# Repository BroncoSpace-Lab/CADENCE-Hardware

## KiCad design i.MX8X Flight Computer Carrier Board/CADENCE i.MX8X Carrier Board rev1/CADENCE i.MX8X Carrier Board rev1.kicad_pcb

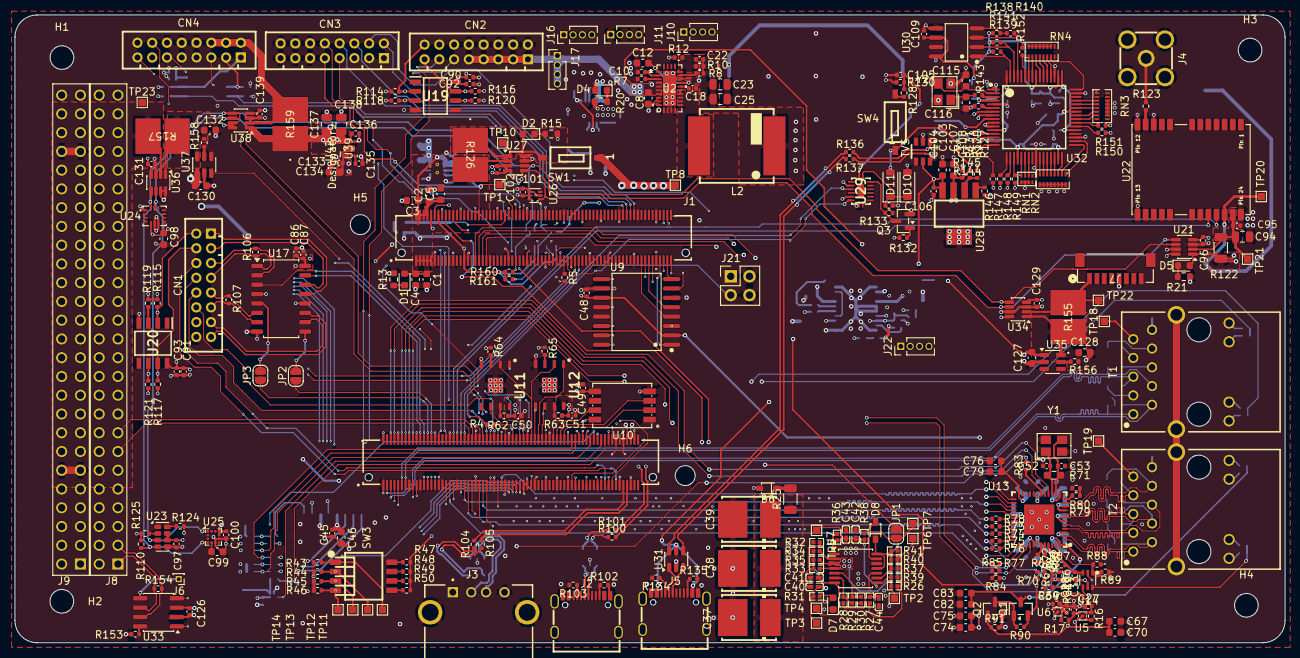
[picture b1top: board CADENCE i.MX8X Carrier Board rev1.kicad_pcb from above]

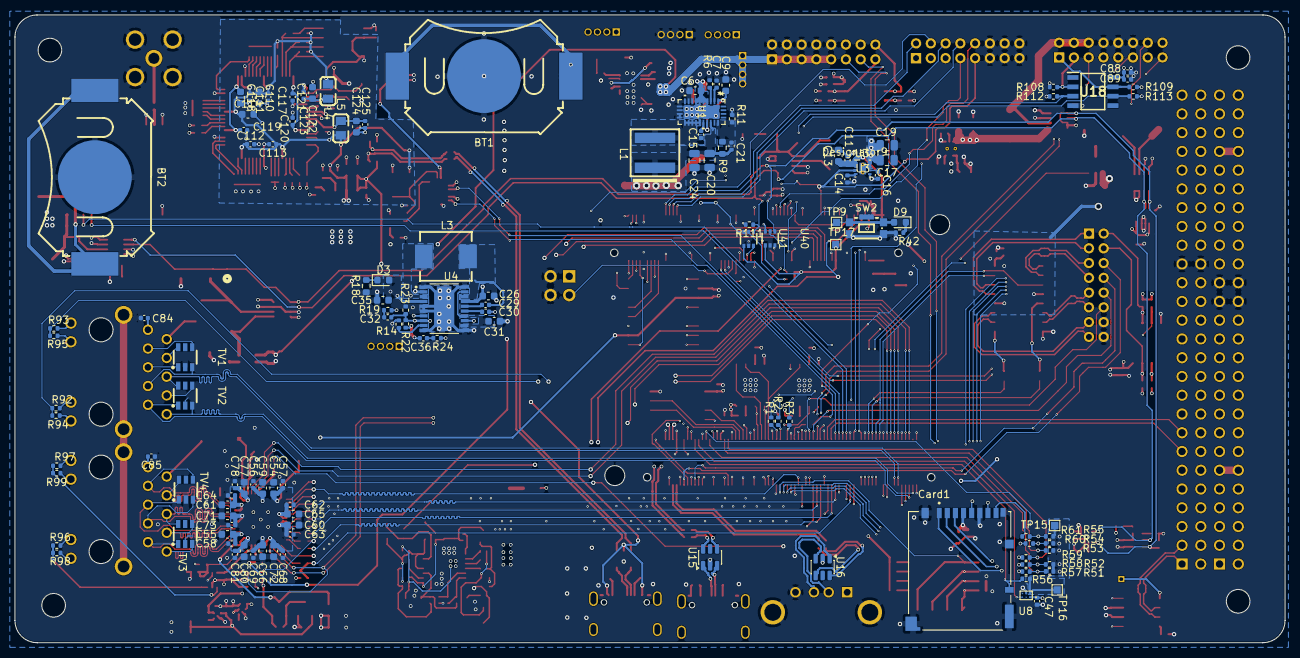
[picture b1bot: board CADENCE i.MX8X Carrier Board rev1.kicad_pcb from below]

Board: 6 copper layers, 172.0 x 85.0 mm, 431 parts (125 on the bottom side), 352 nets.

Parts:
BT1, BT2: Battery_Cell; BAT-SMD_MY-2032-11
C1, C2: 22uF; C_0603_1608Metric
C3, C4, C6, C8, C13, C26, C31, C110, C118, C122, C124, C134: 4.7uF; C_0603_1608Metric
C5, C35, C114: 100nF; C_0603_1608Metric
C7, C10: 10nF; C_0402_1005Metric
C9, C12, C54, C55, C59, C60, C61, C65, C66, C71, C72, C77, C80, C107, C128, C132: 1uF; C_0603_1608Metric
C11, C14, C15, C16, C18, C27, C28, C29, C30, C33, C34, C45, C47, C48, C49, C50, C51, C56, C57, C58, C62, C63, C64, C68, C69, C73, C78, C81, C84, C85, C87, C89, C92, C93, C95, C96, C97, C100, C101, C102, C104, C105, C106, C108, C109, C111, C112, C113, C117, C119, C120, C121, C123, C125, C126, C129, C131, C133, C135, C136, C139: 100nF; C_0402_1005Metric
C17, C19, C137, C138: 22uF; C_0805_2012Metric
C20, C23, C24, C25: 47uF; C_0805_2012Metric
C21: 4.7pF; C_0402_1005Metric
C22: 10pF; C_0402_1005Metric
C32, C86, C88, C90, C91: 1nF; C_0402_1005Metric
C36: 33pF; C_0402_1005Metric
C37, C38, C39: 100uF; CAP-SMD_L7.3-W6.1_TCN4227M025R0100
C40, C41, C42, C43, C44: 10u; C0402
C46, C70, C75, C79, C83, C127, C130: 10uF; C_0603_1608Metric
C52, C53: 18pF; C_0402_1005Metric
C67, C74, C76, C82: 10nF; C_0603_1608Metric
C94: 10u; C_0805_2012Metric
C98: 10u; C_0603_1608Metric
C99: 220nF; C_0603_1608Metric
C103: 2.2uF; C_0603_1608Metric
C115, C116: 12pF; C_0603_1608Metric
CN1, CN2, CN3, CN4: DF11-16DP-2DSA(08); CONN-TH_DF11-16DP-2DSA-08
Card1: HRS DM3BT-DSF-PEJS; HRS_DM3BT-DSF-PEJS
D1, D5, D9: RED; LED_0603_1608Metric
D2, D4, D7: GREEN; LED_0603_1608Metric
D3: BLUE; LED_0603_1608Metric
D6, D8: 1N4448WS-7-F; SOD-323_L1.8-W1.3-LS2.5-RD
D10, D11: MBR0520LT; D_SOD-123
H1, H2, H3, H4: MountingHole; MountingHole_3.2mm_M3
H5, H6: MountingHole; MountingHole_2.7mm_M2.5
J1: BTH-070-02-L-D-A; SAMTEC_BTH-070-02-L-D-A
J2, J5: USB_C_Receptacle_USB2.0_16P; USB-C_SMD-TYPE-C-31-M-12
J3: USB_A; SAMTEC_USB-A-S-X-X-TH
J4: Conn_Coaxial; SMA-TH_132134
J6: Conn_01x01; PinHeader_1x01_P1.00mm_Vertical
J7: Conn_01x08; CONN_BM08B-SRSS-TBLFSN_JST
J8, J9: Conn_02x26_Odd_Even; ESQ-126-39-x-D
J10, J11, J16, J17, J22: Conn_01x04; PinHeader_1x04_P1.27mm_Vertical
J21: Conn_02x02_Odd_Even; PinHeader_2x02_P2.54mm_Vertical
JP1, JP2, JP3: SolderJumper_2_Open; SolderJumper-2_P1.3mm_Open_RoundedPad1.0x1.5mm
L1: 1.8uH; IND-SMD_L6.6-W6.4-P4.04_XAL6030-182MEC
L2: 2.5uH; IND-SMD_L10.9-W10.0
L3: 4.7uH; IND-SMD_L7.0-W6.6
L4, L5: 600R/100MHz; L0805
Q1: IRLML6401; SOT-23
Q2, Q3: BSS138; SOT-23
R1, R2, R3, R4, R5, R57, R58, R59, R60, R61, R73, R74, R75, R76, R77, R96, R123, R136, R137, R146, R147, R148, R149, R150, R151: 22; R_0402_1005Metric
R6, R7: 18.2k; R_0402_1005Metric
R8, R153: 100k; R_0402_1005Metric
R9: 1M; R_0603_1608Metric
R10, R22: 1M; R_0402_1005Metric
R11: 412k; R_0402_1005Metric
R12: 243k; R_0402_1005Metric
R13: 360; R_0603_1608Metric
R14: 23.7k; R_0402_1005Metric
R15: 120; R_0603_1608Metric
R16, R17, R43, R44, R45, R46, R62, R63, R64, R65, R94, R124, R125, R130: 10k; R_0402_1005Metric
R18: 1.47k; R_0603_1608Metric
R19, R24: 15k; R_0402_1005Metric
R20: 470; R_0603_1608Metric
R21: 330; R_0603_1608Metric
R23: 90.9k; R_0402_1005Metric
R25: 10; R_1206_3216Metric
R26, R27, R28, R29, R32, R33: 10k; R0402
R30, R31: 3k; R0402
R34, R36: 1k; R0402
R35, R37, R38, R40, R41: 100k; R0402
R39: 4.7M; R0402
R42: 43; R_0402_1005Metric
R47, R48, R49, R50: 1k; R_0402_1005Metric
R51, R52, R53, R54, R55, R56: 49.9k; R_0402_1005Metric
R66, R140: 2K; R_0402_1005Metric
R67, R72, R80, R86, R90, R91, R95, R99, R127, R129, R132, R133, R138, R139, R141, R145, R160, R161: 10K; R_0402_1005Metric
R68, R69, R70, R82, R85, R87, R89, R98: 2.49K; R_0402_1005Metric
R71: 1M; R_0603_1608Metric_Pad0.98x0.95mm_HandSolder
R78: 0; R_0402_1005Metric
R79, R144, R152: 1K; R_0402_1005Metric
R81, R84, R88: 5.76K; R_0402_1005Metric
R83: 49.9; R_0402_1005Metric
R92, R93, R97, R143: 200; R_0402_1005Metric
R100, R101, R104, R105: 27; R_0402_1005Metric
R102, R103, R134, R135: 5.1k; R_0402_1005Metric
R106, R107, R154: 120; R_0402_1005Metric
R108, R109, R114, R115, R116, R117: 330; R_0402_1005Metric
R110, R111, R112, R113, R118, R119, R120, R121: 4.7k; R_0402_1005Metric
R122: 0.002; R_1206_3216Metric
R126, R155, R157, R159: 0.002; RES_WSHM2818_VIS
R128: 100; R_0402_1005Metric
R131: 16.5K; R_0402_1005Metric
R142: 12K; R_0402_1005Metric
R156, R158: 150; R_0402_1005Metric
RN1: 4D02WGJ0103TCE; RES-ARRAY-SMD_0402-8P-L2.0-W1.0-BL
RN2, RN3, RN4: 16P8WGJ103T4E; RES-ARRAY-SMD_0402-16P-L4.0-W1.6-BL
SW1, SW4: SW_DIP_x01; SW-SMD_1.27-1P-TPPT
SW2: KMR221GLFS; KEY-SMD_KMR2XXGXXX
SW3: SW_DIP_x04; SW-SMD_8P-L11.3-W6.2-P1.27-LS8.2
T1, T2: WE-RJ45_7499111121A; 7499111121A
TP1, TP2, TP3, TP4, TP5, TP6, TP7, TP8, TP9, TP10, TP11, TP12, TP13, TP14, TP15, TP16, TP17, TP18, TP19, TP20, TP21, TP22, TP23: TestPoint; TestPoint_Pad_1.0x1.0mm
TV1, TV2, TV3, TV4, TV5: SRV05-4.TCT; SOT-23-6_L2.9-W1.6-P0.95-LS2.8-BR
U1, U2: LT8612; QFN-28_UDE_LTI
U3, U39: TPS22975; DSG0008B
U4: LT3115-1; CONV_LTC3115EFE-1_PBF
U5: TLV71325PDQNR; X2SON-4_L1.0-W1.0-P0.65-TL-EP
U6: TLV71310PDQNR; X2SON-4_L1.0-W1.0-P0.65-TL-EP
U7: TLV1704; TSSOP-14_4.4x5mm_P0.65mm
U8: BD2204GUL-E2; BGA-6_L1.5-W1.0-P0.50_BD2204GUL-E2
U9: MX25UM51245G; SOP-16_L10.3-W7.5-P1.27-LS10.3-BL
U10: ZDSD04GLGEAG; LGA-8_L8.0-W6.0-P1.27-TL-1
U11, U12: MR20H40; SON127P600X500X90-9N-D
U13: DP83867IRRGZR; VQFN-48_L7.0-W7.0-P0.50-BL-EP4.1
U14: 74LVC2G07; SOT-363_L2.1-W1.3-P0.65-LS2.2-BL
U15, U16, U31: USBLC6-2SC6; SOT-23-6
U17: SN65C1168ERGYR; SOP-16_4.55x10.3mm_P1.27mm
U18, U19, U20: P82B715DR; SOIC127P600X175-8N
U21, U27, U34, U36, U38: INA219AxDCN; SOT-23-8
U22: Skytraq Orion B16 GPS
U23: RV-3028-C7; MicroCrystal_C7_SON-8_1.5x3.2mm_P0.9mm
U24: LSM6DSO; LGA-14_L3.0-W2.5-P0.50-TL
U25: IIS2MDCTR; LGA-12_2x2mm_P0.5mm
U26: TMP112xxDRL; SOT-563
U28: LP38693MP-ADJ/NOPB; SOT-223-5_L6.5-W3.5-P1.50-LS7.0-BL
U29: 74CBTLV3257BQ; 74CBTLV3257BQ115
U30: CAT93C66VI-GT3; SOIC-8_L4.9-W3.9-P1.27-LS6.0-BL
U32: FT2232HL; LQFP-64_L10.0-W10.0-P0.50-LS12.0-TL
U33: SN65HVD233; SOIC-8_3.9x4.9mm_P1.27mm
U35, U37: TPS22810DBV; SOT-23-6
U40, U41: TXS0101DCKR; SC-70-6_L2.0-W1.3-P0.65-LS2.1-BR
Y1: 25MHz; CRYSTAL-SMD_4P-L3.2-W2.5-BL-2
Y2: 12MHz; CRYSTAL-SMD_4P-L3.2-W2.5-BL

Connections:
1V8_FTDI: C118.1, C119.1, C120.1, C121.1, U32.12 (VCORE), U32.37 (VCORE), U32.49 (VREGOUT), U32.64 (VCORE)
3V3_FTDI: C107.1, C108.1, C109.1, C110.1, C111.1, C112.1, C113.1, C114.1, C117.1, D11.2 (A), L4.1, L5.1, R131.1, R138.1, R139.1, R141.1, R144.2, R152.1, SW4.1, U28.3 (OUT), U30.6 (ORG), U30.8 (VCC), U32.20 (VCCIO), U32.31 (VCCIO), U32.42 (VCCIO), U32.50 (VREGIN), U32.56 (VCCIO)
3V3_FTDI_VPHY: C122.1, C123.1, L4.2, U32.4 (VPHY)
3V3_FTDI_VPLL: C124.1, C125.1, L5.2, U32.9 (VPLL)
5V Power Good: R8.2, U2.23 (PG)
12V_SYNC: C31.2, U4.9 (VCC), U4.11 (PVCC), U4.16 (PWM/SYNC)
+3.3V: C17.2, C19.2, C45.1, C46.1, C47.1, C49.1, C50.1, C51.1, C88.1, C89.1, C90.1, C91.1, C92.1, C93.1, C96.1, C97.1, C98.1, C100.1, C101.1, C102.1, C126.1, C129.1, C131.1, C133.1, C134.1, C139.1, Card1.4 (VDD), D5.2 (A), D6.2 (A), D10.2 (A), J10.1, J10.2, J10.3, J10.4, R62.2, R63.2, R64.2, R65.2, R94.1, R95.1, R98.1, R99.1, R108.2, R109.2, R110.2, R111.2, R112.2, R113.2, R114.2, R115.2, R116.2, R117.2, R118.2, R119.2, R120.2, R121.2, R122.1, R124.2, R125.2, R132.1, T1.11, T1.13, T2.11, T2.13, U3.7 (VOUT_1), U3.8 (VOUT_2), U8.A1 (VIN1), U10.5 (VDD), U11.8 (VDD), U12.8 (VDD), U18.8 (Vcc), U19.8 (Vcc), U20.8 (Vcc), U21.1 (IN+), U21.4 (VS), U21.8 (A1), U23.6 (VBACKUP), U23.7 (VDD), U24.5 (VDDIO), U24.8 (VDD), U25.9 (Vdd), U25.10 (Vdd_IO), U26.5 (V+), U27.4 (VS), U33.3 (VCC), U34.4 (VS), U36.4 (VS), U36.7 (A0), U36.8 (A1), U38.4 (VS), U39.1 (VIN_1), U39.2 (VIN_2)
+5V: C6.1, C22.2, C23.1, C25.1, C86.1, C87.1, D4.2 (A), J16.1, J16.2, J16.3, J16.4, L2.2, R8.1, R10.2, U1.4 (EN/UV), U1.5 (VIN), U1.6 (VIN), U1.7 (VIN), U2.22 (BIAS), U17.4 (1DE), U17.12 (2DE), U17.16 (VCC)
+12V: C35.2, C36.2, D3.2 (A), J22.1, J22.2, J22.3, J22.4, R22.2, U4.3 (PVOut)
/External Board Connections/ADCS_P3V3: CN4.2, CN4.4, CN4.6, R159.2, U38.2 (IN-)
/External Board Connections/ADCS_PWR_MONITOR: C137.2, C138.2, R159.1, U38.1 (IN+), U39.7 (VOUT_1), U39.8 (VOUT_2)
/External Board Connections/CAN+: J8.3, R154.1, U33.7 (CANH)
/External Board Connections/CAN-: J8.1, R154.2, U33.6 (CANL)
/External Board Connections/IMAGER_PWR: J7.1, R155.2, TP22.1 (1_1), U34.2 (IN-)
/External Board Connections/IMAGER_PWR_MONITOR: C128.1, R155.1, R156.2, U34.1 (IN+), U35.6 (VOUT)
/External Board Connections/SATNOGS_PWR: J9.11, J9.12, J9.45, J9.46, R157.2, TP23.1 (1_1), U36.2 (IN-)
/External Board Connections/SATNOGS_PWR_MONITOR: C132.1, R157.1, R158.2, U36.1 (IN+), U37.6 (VOUT)
/FTDI/ACBUS0: RN2.8, U32.26 (ACBUS0)
/FTDI/ACBUS1: RN2.7, U32.27 (ACBUS1)
/FTDI/ACBUS2: RN2.6, U32.28 (ACBUS2)
/FTDI/ACBUS3: RN2.5, U32.29 (ACBUS3)
/FTDI/ACBUS4: RN2.4, U32.30 (ACBUS4)
/FTDI/ACBUS5: RN2.3, U32.32 (ACBUS5)
/FTDI/ACBUS6: RN2.2, U32.33 (ACBUS6)
/FTDI/ACBUS7: RN2.1, U32.34 (ACBUS7)
/FTDI/BCBUS0: RN4.7, U32.48 (BCBUS0)
/FTDI/BCBUS1: RN4.6, U32.52 (BCBUS1)
/FTDI/BCBUS2: RN4.5, U32.53 (BCBUS2)
/FTDI/BCBUS3: RN4.4, U32.54 (BCBUS3)
/FTDI/BCBUS4: RN4.3, U32.55 (BCBUS4)
/FTDI/BCBUS5: RN4.2, U32.57 (BCBUS5)
/FTDI/BCBUS6: RN4.1, U32.58 (BCBUS6)
/FTDI/BDBUS2: RN3.7, U32.40 (BDBUS2)
/FTDI/BDBUS3: RN3.6, U32.41 (BDBUS3)
/FTDI/BDBUS4: RN3.5, U32.43 (BDBUS4)
/FTDI/BDBUS5: RN3.4, U32.44 (BDBUS5)
/FTDI/BDBUS6: RN3.3, U32.45 (BDBUS6)
/FTDI/DEBUG_USB_DN: R136.2, TV5.1, U32.7 (DM)
/FTDI/DEBUG_USB_DP: R137.2, TV5.6, U32.8 (DP)
/FTDI/FTDI D+: J5.A6 (D+), J5.B6 (D+), U31.3 (I/O2)
/FTDI/FTDI D-: J5.A7 (D-), J5.B7 (D-), U31.1 (I/O1)
/FTDI/FTDI USB+: R137.1, U31.4 (I/O2)
/FTDI/FTDI USB-: R136.1, U31.6 (I/O1)
/FTDI/FTDI_OSCI: C115.2, U32.2 (OSCI), Y2.3
/FTDI/FTDI_OSCO: C116.2, R143.2, Y2.1
/FTDI/MUX_BUFF_OE: Q3.3 (D), R133.2, U29.15 (~OE)
/FTDI/X_UART0_RX_FTDI: R150.1, U29.3 (1B2)
/FTDI/X_UART0_TX_FTDI: R151.1, U29.6 (2B2)
/FTDI/enable_ftdi: C105.1, R128.2, R130.2, U29.1 (S)
/GPS/GPS VCC: C94.1, C95.1, R122.2, TP21.1 (1_1), U21.2 (IN-), U22.23 (VCC)
/Power/3v3 Feedback: C21.1, R9.1, R11.1, U1.24 (FB)
/Power/3v3 SW: C15.1, L1.1, U1.15 (SW), U1.16 (SW), U1.17 (SW), U1.18 (SW), U1.19 (SW)
/Power/5V FB: C22.1, R10.1, R12.2, U2.24 (FB)
/Power/5v SW: C18.1, L2.1, U2.15 (SW), U2.16 (SW), U2.17 (SW), U2.18 (SW), U2.19 (SW)
/Power/12V_SW1: C29.2, L3.1, U4.15 (SW1)
/Power/12V_SW2: C30.2, L3.2, U4.2 (SW2)
/RS422/RS422_CTSN: CN1.15, U17.11 (2Z)
/RS422/RS422_CTSP: CN1.13, U17.10 (2Y)
/RS422/RS422_RTSN: CN1.11, R107.1, U17.7 (2B)
/RS422/RS422_RTSP: CN1.9, R107.2, U17.6 (2A)
/RS422/RS422_RXN: CN1.7, R106.1, U17.1 (1B)
/RS422/RS422_RXP: CN1.5, R106.2, U17.2 (1A)
/RS422/RS422_TXN: CN1.3, U17.14 (1Y)
/RS422/RS422_TXP: CN1.1, U17.13 (1Z)
/USB OTG/USBA1 D+: J3.3 (D+), U16.1 (I/O1)
/USB OTG/USBA1 D-: J3.2 (D-), U16.3 (I/O2)
/USB OTG/USBA2 D+: R104.1, U16.6 (I/O1)
/USB OTG/USBA2 D-: R105.1, U16.4 (I/O2)
/USB OTG/USBC1 D+: J2.A6 (D+), J2.B6 (D+), U15.3 (I/O2)
/USB OTG/USBC1 D-: J2.A7 (D-), J2.B7 (D-), U15.1 (I/O1)
/USB OTG/USBC2 D+: R101.1, U15.4 (I/O2)
/USB OTG/USBC2 D-: R100.1, U15.6 (I/O1)
/Watchdog/TLV1704B+: C41.2, R34.1, R35.2, TP4.1 (1_1), U7.7 (+)
/Watchdog/WDT-VIN: C37.1, C38.1, C39.1, R25.2, R26.2, R35.1, R41.1, TP2.1 (1_1), U7.3 (V+)
/Watchdog/WDT-VP: R29.1, R30.2, U7.5 (+)
CAN_INPUT_TEST: J6.1 (Pin_1_1), U33.5 (LBK)
ETH1_A_TX_N: T2.2 (D1-), TV3.1, U13.2 (TD_M_A)
ETH1_A_TX_P: T2.1 (D1+), TV3.3, U13.1 (TD_P_A)
ETH1_B_TX_N: T2.6 (D2-), TV4.1, U13.5 (TD_M_B)
ETH1_B_TX_P: T2.3 (D2+), TV3.4, U13.4 (TD_P_B)
ETH1_C_TXCLK_N: T2.5 (D3-), TV3.6, U13.8 (TD_M_C)
ETH1_C_TXCLK_P: T2.4 (D3+), TV4.3, U13.7 (TD_P_C)
ETH1_D_RXDV_N: T2.8 (D4-), TV4.4, U13.11 (TD_M_D)
ETH1_D_RXDV_P: T2.7 (D4+), TV4.6, U13.10 (TD_P_D)
ETH1_LED0: R96.1, R98.2, U14.6 (1Y)
ETH1_LED1: R97.2, R99.2, U14.4 (2Y)
GND: BT1.2 (-), BT2.2 (-), C1.2, C2.2, C3.2, C4.2, C5.2, C6.2, C7.1, C8.2, C9.1, C10.1, C11.2, C12.1, C13.2, C14.2, C16.2, C17.1, C19.1, C20.2, C23.2, C24.2, C25.2, C26.1, C27.2, C28.2, C31.1, C33.2, C34.2, C35.1, C37.2, C38.2, C39.2, C41.1, C42.1, C43.1, C44.1, C45.2, C46.2, C47.2, C48.2, C49.2, C50.2, C51.2, C52.1, C53.1, C54.2, C55.2, C56.2, C57.2, C58.2, C59.2, C60.2, C61.2, C62.2, C63.2, C64.2, C65.2, C66.2, C67.2, C68.2, C69.2, C70.2, C71.2, C72.2, C73.2, C74.2, C75.2, C76.2, C77.2, C78.2, C79.2, C80.2, C81.2, C82.2, C83.2, C84.1, C85.1, C86.2, C87.2, C88.2, C89.2, C90.2, C91.2, C92.2, C93.2, C94.2, C95.2, C96.2, C97.2, C98.2, C99.2, C100.2, C101.2, C102.2, C103.2, C104.2, C105.2, C106.2, C107.2, C108.2, C109.2, C110.2, C111.2, C112.2, C113.2, C114.2, C115.1, C116.1, C117.2, C118.2, C119.2, C120.2, C121.2, C122.2, C123.2, C124.2, C125.2, C126.2, C127.2, C128.2, C129.2, C130.2, C131.2, C132.2, C133.2, C134.2, C135.2, C136.2, C137.1, C138.1, C139.2, CN1.14, CN1.16, CN2.2, CN2.4, CN2.6, CN2.8, CN2.10, CN3.11, CN3.12, CN3.13, CN3.14, CN3.15, CN3.16, CN4.8, CN4.10, CN4.12, Card1.6 (VSS), Card1.10 (DET), Card1.11 (SHELL), Card1.12 (SHELL), Card1.13 (SHELL), Card1.14 (SHELL), D7.1 (K), J1.A2 (GND), J1.A5 (GND), J1.A7 (GND), J1.A12 (GND), J1.A20 (GND), J1.A25 (GND), J1.A31 (GND), J1.A36 (GND), J1.A40 (GND), J1.A45 (GND), J1.A52 (GND), J1.A56 (GND), J1.A61 (GND), J1.A66 (GND), J1.A70 (GND), J1.B3 (GND), J1.B6 (GND), J1.B9 (GND), J1.B12 (GND), J1.B15 (GND), J1.B18 (GND), J1.B20 (GND), J1.B23 (GND), J1.B26 (GND), J1.B29 (GND), J1.B32 (GND), J1.B37 (GND), J1.B40 (GND), J1.B45 (GND), J1.B50 (GND), J1.B54 (GND), J1.B60 (GND), J1.B63 (GND), J1.B70 (GND), J1.C5 (GND), J1.C10 (GND), J1.C15 (GND), J1.C20 (GND), J1.C25 (GND), J1.C30 (GND), J1.C35 (GND), J1.C40 (GND), J1.C45 (GND), J1.C48 (GND), J1.C54 (GND), J1.C58 (GND), J1.C63 (GND), J1.D5 (GND), J1.D11 (GND), J1.D18 (GND), J1.D23 (GND), J1.D28 (GND), J1.D31 (GND), J1.D35 (GND), J1.D40 (GND), J1.D45 (GND), J1.D50 (GND), J1.D56 (GND), J1.D60 (GND), J1.D65 (GND), J2.A1 (GND), J2.A12 (GND), J2.B1 (GND), J2.B12 (GND), J3.4 (GND), J3.5 (Shield), J4.2 (Ext), J5.A1 (GND), J5.A12 (GND), J5.B1 (GND), J5.B12 (GND), J7.5, J8.33, J8.34, J9.29, J9.30, J9.31, J9.32, J11.1, J11.2, J11.3, J11.4, J21.2, J21.4, Q2.2 (S), Q3.2 (S), R6.2, R7.2, R11.2, R12.1, R13.2, R14.1, R15.2, R18.2, R20.2, R21.2, R23.1, R30.1, R32.1, R42.2, R43.2, R44.2, R45.2, R46.2, R68.2, R70.2, R72.2, R80.2, R82.2, R85.2, R87.2, R89.2, R91.2, R102.2, R103.2, R129.2, R130.1, R134.2, R135.2, R142.2, R145.2, R153.2, RN1.6, RN1.7, RN1.8, RN2.9, RN2.10, RN2.11, RN2.12, RN2.13, RN2.14, RN2.15, RN2.16, RN3.10, RN3.11, RN3.12, RN3.13, RN3.14, RN4.10, RN4.11, RN4.12, RN4.13, RN4.14, RN4.15, RN4.16, SW2.3, SW2.4, TV1.2, TV2.2, TV3.2, TV4.2, TV5.2, U1.8 (PGND), U1.9 (PGND), U1.10 (PGND), U1.11 (GND), U1.12 (GND), U1.13 (GND), U1.14 (GND), U2.8 (PGND), U2.9 (PGND), U2.10 (PGND), U2.11 (GND), U2.12 (GND), U2.13 (GND), U2.14 (GND), U3.5 (GND), U4.4 (GND), U4.5 (GND), U4.17 (PGND), U5.2 (GND), U5.5 (PAD), U6.2 (GND), U6.5 (PAD), U7.12 (V-), U8.B2 (GND), U9.6 (GND), U9.10 (GND), U10.4 (GND), U11.4 (VSS), U11.9 (PAD), U12.4 (VSS), U12.9 (PAD), U13.49 (GND), U14.2 (GND), U15.2 (GND), U16.2 (GND), U17.8 (GND), U18.4 (GND), U19.4 (GND), U20.4 (GND), U21.3 (GND), U21.7 (A0), U22.10 (GND), U22.12 (GND), U22.13 (GND), U22.24 (GND), U23.5 (VSS), U24.1 (SDO/SA0), U24.6 (GND), U24.7 (GND), U25.6 (GND), U25.8 (GND), U26.2 (GND), U26.4 (ADD0), U27.3 (GND), U27.7 (A0), U27.8 (A1), U28.5 (GND), U29.8 (GND), U30.5 (GND), U31.2 (GND), U32.1 (GND), U32.5 (GND), U32.10 (AGND), U32.11 (GND), U32.15 (GND), U32.25 (GND), U32.35 (GND), U32.47 (GND), U32.51 (GND), U33.2 (GND), U34.3 (GND), U34.7 (A0), U35.2 (GND), U36.3 (GND), U37.2 (GND), U38.3 (GND), U39.5 (GND), U40.2 (GND), U41.2 (GND), Y1.2, Y1.4, Y2.2, Y2.4
GNDPWR: T1.S1 (SHIELD1), T1.S2 (SHIELD2), T2.S1 (SHIELD1), T2.S2 (SHIELD2)
GPIO0_IO19: CN2.12, J1.A53 (X_MCLK_IN0)
GPIO0_IO20: CN2.14, J1.A55 (X_MCLK_OUT0)
GPIO0_IO30: CN4.7, J1.A38 (X_SAI1_RXC)
GPIO0_IO31: CN4.5, J1.A39 (X_SAI1_RXFS)
GPIO1_15: CN1.10, J1.A42 (X_FLEXCAN0_RX)
GPIO1_16: CN1.12, J1.A41 (X_FLEXCAN0_TX)
GPIO1_25: CN3.2, J1.C12 (X_MIPI_DSI0_I2C0_SCL)
GPIO1_26: CN3.4, J1.C11 (X_MIPI_DSI0_I2C0_SDA)
GPIO1_27: CN3.6, J1.C13 (X_MIPI_DSI0_GPIO0_00)
GPIO1_28: CN3.8, J1.C14 (X_MIPI_DSI0_GPIO0_01)
GPIO1_29: J1.C41 (X_MIPI_DSI1_I2C0_SCL), J21.1
GPIO1_30: CN3.10, J1.C42 (X_MIPI_DSI1_I2C0_SDA)
GPIO3_01: J1.D29 (X_CSI_MCLK), J21.3
GPIO3_IO14: J1.C1 (X_QSPI0A_SS0_B), U9.3 (RESET#)
GPIO4_03: CN1.6, J1.B7 (X_USB3_SS3_TC0)
GPIO4_05: CN1.8, J1.B10 (X_USB3_SS3_TC2)
GPIO4_IO00: J1.B19 (X_PCIE_CTRL_PERST_B), U37.3 (EN/UVLO)
GPIO4_IO01: CN2.13, J1.B30 (X_PCIE_CTRL_CLKREQ_B)
GPIO4_IO02: CN2.11, J1.B31 (X_PCIE_CTRL_WAKE_B)
GPIO4_IO20: CN4.11, J1.A8 (X_USDHC1_VSELECT/NAND_RE_P)
GPIO4_IO21: CN4.9, J1.A9 (X_USDHC1_WP/NAND_DQS_N)
HS_I2C0_SCL: R111.1, U21.5 (SCL), U23.3 (SCL), U24.13 (SCL), U25.1 (SCL/SPC), U26.1 (SCL), U27.5 (SCL), U34.6 (SDA), U36.6 (SDA), U38.6 (SDA), U41.4 (B)
HS_I2C0_SCL_1V8: J1.D33 (X_MIPI_CSI0_GPIO0_00), U41.3 (A)
HS_I2C0_SDA: R110.1, U21.6 (SDA), U23.4 (SDA), U24.14 (SDA), U25.4 (SDA/SDI/SDO), U26.6 (SDA), U27.6 (SDA), U34.5 (SCL), U34.8 (A1), U36.5 (SCL), U38.5 (SCL), U38.7 (A0), U38.8 (A1), U40.4 (B)
HS_I2C0_SDA_1V8: J1.D34 (X_MIPI_CSI0_GPIO0_01), U40.3 (A)
HS_I2C1_LCL: CN2.15, R116.1, U19.7 (Ly)
HS_I2C1_LDA: CN2.16, R114.1, U19.2 (Lx)
HS_I2C1_SCL: J1.B8 (X_USB3_SS3_TC1), R120.1, U19.6 (Sy)
HS_I2C1_SDA: J1.B11 (X_USB3_SS3_TC3), R118.1, U19.3 (Sx)
HS_I2C2_LCL: CN4.1, R109.1, U18.7 (Ly)
HS_I2C2_LDA: CN4.3, R108.1, U18.2 (Lx)
HS_I2C2_SCL: J1.C43 (X_MIPI_DSI1_GPIO0_00), R113.1, U18.6 (Sy)
HS_I2C2_SDA: J1.C44 (X_MIPI_DSI1_GPIO0_01), R112.1, U18.3 (Sx)
HS_I2C3_LCL: CN1.4, R117.1, U20.7 (Ly)
HS_I2C3_LDA: CN1.2, R115.1, U20.2 (Lx)
HS_I2C3_SCL: J1.D26 (X_CSI_EN), R121.1, U20.6 (Sy)
HS_I2C3_SDA: J1.D27 (X_CSI_RESET), R119.1, U20.3 (Sx)
LED0_LINK: R88.2, R89.1, U13.47 (LED_0), U14.1 (1A)
LED2_ACT: R86.2, R87.1, U13.45 (LED_2), U14.3 (2A)
unnamed: BT1.1 (+), J1.C66 (VBAT)
unnamed: BT2.1 (+), TP20.1 (1_1), U22.22 (V_Backup)
unnamed: C32.2, R19.1
unnamed: C36.1, R24.2
unnamed: C40.2, R32.2, R33.2
unnamed: Card1.2 (CD/DAT3), R58.1
unnamed: Card1.3 (CMD), R59.1
unnamed: Card1.7 (DAT0), R60.1
unnamed: Card1.8 (DAT1), R61.1
unnamed: Card1.1 (DAT2), R57.1
unnamed: D1.1 (K), R13.1
unnamed: D2.1 (K), R15.1
unnamed: D3.1 (K), R18.1
unnamed: D4.1 (K), R20.1
unnamed: D5.1 (K), R21.1
unnamed: D6.1 (C), R25.1
unnamed: D7.2 (A), R31.1
unnamed: D8.2 (A), R38.2
unnamed: D8.1 (C), R39.2, R40.2, R41.2, TP6.1 (1_1), U7.11 (+), U7.14
unnamed: D9.1 (K), R42.1
unnamed: C106.1, D10.1 (K), D11.1 (K), R133.1, U29.16 (VCC)
unnamed: J1.A32 (X_SAI0_RXD), R1.2
unnamed: J1.A35 (X_SAI0_TXC), R3.2
unnamed: J1.A33 (X_SAI0_TXD), R2.2
unnamed: J1.A37 (X_SAI1_RXD), R4.2
unnamed: J1.D30 (X_CSI_PCLK), R5.1
unnamed: J2.A5 (CC1), R103.1
unnamed: J2.B5 (CC2), R102.1
unnamed: J4.1 (In), R123.2
unnamed: J5.A5 (CC1), R134.1
unnamed: J5.B5 (CC2), R135.1
unnamed: JP1.1 (A), TP7.1 (1_1), U7.13
unnamed: JP2.2 (B), U17.9 (2D)
unnamed: JP3.2 (B), U17.5 (2R)
unnamed: C77.1, C78.1, C80.1, C81.1, C82.1, C83.1, Q1.3 (D), U13.13 (VDDA1P8), U13.48 (VDDA1P8)
unnamed: Q1.1 (G), Q2.3 (D), R90.2
unnamed: Q3.1 (G), R132.2
unnamed: R26.1, R27.2, R37.1
unnamed: R34.2, U7.2
unnamed: R36.2, U7.1
unnamed: R47.2, SW3.8
unnamed: R48.2, SW3.7
unnamed: R49.2, SW3.6
unnamed: R50.2, SW3.5
unnamed: R79.2, R80.1
unnamed: R92.2, T1.12
unnamed: R93.1, T1.14
unnamed: R96.2, T2.12
unnamed: R97.1, T2.14
unnamed: R128.1, SW4.2
unnamed: C84.2, T1.10 (GND)
unnamed: T1.9 (VCC), TP18.1 (1_1)
unnamed: C85.2, T2.10 (GND)
unnamed: T2.9 (VCC), TP19.1 (1_1)
unnamed: C15.2, U1.20 (BST)
unnamed: C9.2, U1.1 (SYNC), U1.21 (INTVCC)
unnamed: R6.1, U1.3 (RT)
unnamed: C7.2, U1.2 (TR/SS)
unnamed: C18.2, U2.20 (BST)
unnamed: C12.2, U2.1 (SYNC), U2.21 (INTVCC)
unnamed: R7.1, U2.3 (RT)
unnamed: C10.2, U2.2 (TR/SS)
unnamed: C16.1, U3.6 (CT)
unnamed: C14.1, U3.4 (VBIAS)
unnamed: C29.1, U4.12 (BST1)
unnamed: C30.1, U4.13 (BST2)
unnamed: C32.1, R22.1, R23.2, R24.1, U4.6 (FB)
unnamed: R14.2, U4.8 (RT)
unnamed: R19.2, U4.7 (VC)
unnamed: R16.2, U5.3 (EN)
unnamed: R17.2, U6.3 (EN)
unnamed: R33.1, U7.4 (-)
unnamed: R28.1, R29.2, U7.6 (-)
unnamed: R37.2, R40.1, U7.9 (+)
unnamed: C42.2, C43.2, R36.1, R38.1, R39.1, TP5.1 (1_1), U7.8 (-)
unnamed: C44.2, R27.1, R28.2, U7.10 (-)
unnamed: R62.1, U11.7 (~HOLD)
unnamed: R64.1, U11.3 (~WP)
unnamed: R63.1, U12.7 (~HOLD)
unnamed: R65.1, U12.3 (~WP)
unnamed: R83.2, U13.18 (CLK_OUT)
unnamed: R79.1, U13.12 (RBIAS)
unnamed: R72.1, U13.43 (RESET_N)
unnamed: R78.1, U13.32 (RX_CLK)
unnamed: R77.1, U13.38 (RX_CTRL)
unnamed: R73.1, U13.33 (RX_D0)
unnamed: R74.1, U13.34 (RX_D1)
unnamed: R75.1, U13.35 (RX_D2)
unnamed: R76.1, U13.36 (RX_D3)
unnamed: C52.2, R71.1, U13.15 (X_I), Y1.1
unnamed: C53.2, R71.2, U13.14 (X_O), Y1.3
unnamed: R123.1, U22.11 (RF_IN)
unnamed: R124.1, U23.8 (EVI)
unnamed: R125.1, U23.2 (~INT)
unnamed: C99.1, U25.5 (C1)
unnamed: R129.1, R131.2, U28.2 (ADJ)
unnamed: R127.1, U28.1 (EN)
unnamed: R139.2, U30.1 (CS), U32.63 (EECS)
unnamed: R140.1, U30.3 (DI), U32.61 (EEDATA)
unnamed: R138.2, R140.2, U30.4 (DO)
unnamed: R141.2, U30.2 (SK), U32.62 (EECLK)
unnamed: R146.2, U32.16 (ADBUS0)
unnamed: R147.2, U32.17 (ADBUS1)
unnamed: R148.2, U32.18 (ADBUS2)
unnamed: R149.2, U32.19 (ADBUS3)
unnamed: RN1.1, U32.21 (ADBUS4)
unnamed: RN1.2, U32.22 (ADBUS5)
unnamed: RN1.3, U32.23 (ADBUS6)
unnamed: R152.2, U32.59 (BCBUS7)
unnamed: R150.2, U32.38 (BDBUS0)
unnamed: R151.2, U32.39 (BDBUS1)
unnamed: R143.1, U32.3 (OSCO)
unnamed: R142.1, U32.6 (REF)
unnamed: R145.1, U32.13 (TEST)
unnamed: R144.1, U32.14 (~RESET)
unnamed: R153.1, U33.8 (Rs)
unnamed: R156.1, U35.5 (QOD)
unnamed: R158.1, U37.5 (QOD)
unnamed: C136.1, U39.6 (CT)
unnamed: C135.1, U39.4 (VBIAS)
unnamed: R160.2, U40.5 (OE)
unnamed: R161.2, U41.5 (OE)
P_1V8_OUT: C28.1, C48.1, C56.1, C59.1, C62.1, C65.1, C68.1, C72.1, C74.1, C75.1, J1.C64 (VCC_1V8), J1.D57 (VDD_ADC_1V8), Q1.2 (S), R47.1, R48.1, R49.1, R50.1, R67.1, R69.1, R81.1, R84.1, R86.1, R88.1, R90.1, R160.1, R161.1, TP17.1 (1_1), U6.4 (IN), U9.2 (VCC), U9.11 (VCC), U13.19 (VDDIO), U13.30 (VDDIO), U13.41 (VDDIO), U14.5 (VCC), U40.1 (VCCA), U41.1 (VCCA)
P_3V3: C1.1, C2.1, C3.1, C4.1, C5.1, C11.1, C13.1, D1.2 (A), J1.C67 (VCC), J1.C68 (VCC), J1.C69 (VCC), J1.C70 (VCC), J1.D66 (VCC), J1.D67 (VCC), J1.D68 (VCC), J1.D69 (VCC), J1.D70 (VCC), R126.2, U3.1 (VIN_1), U3.2 (VIN_2), U27.2 (IN-)
P_3V3_OUT: C27.1, J1.C65 (VCC_3V3), R16.1, R66.2, U5.4 (IN), U40.6 (VCCB), U41.6 (VCCB)
Power_Switch_Output: D2.2 (A), R126.1, SW1.2, TP10.1 (1_1), U27.1 (IN+)
Regulator_Output: C20.1, C21.2, C24.1, L1.2, R9.2, SW1.1, TP8.1 (1_1), U1.22 (BIAS)
SCU_WDOG0_WDOG_OUT: C40.1, J1.C62 (X_SCU_GPIO0_01), R31.2, TP3.1 (1_1)
SPI1_CS0: J8.9, R1.1
SPI1_CS1: CN3.1, R4.1
SPI1_SCK: CN3.7, J8.11, R5.2
SPI1_SDI: CN3.5, J8.12, R3.1
SPI1_SDO: CN3.3, J8.10, R2.1
VBAT: C8.1, C26.2, C127.1, C130.1, CN2.1, CN2.3, CN2.5, CN2.7, CN2.9, J17.1, J17.2, J17.3, J17.4, U2.4 (EN/UV), U2.5 (VIN), U2.6 (VIN), U2.7 (VIN), U4.1 (RUN), U4.10 (Vin), U4.14 (PVin), U35.1 (VIN), U37.1 (VIN)
VBUS_DEBUG_USB: C103.1, C104.1, J5.A4 (VBUS), J5.A9 (VBUS), J5.B4 (VBUS), J5.B9 (VBUS), TV5.5, U28.4 (IN), U31.5 (VBUS)
VCC_LDO_SD1: J1.A17 (VCC_LDO_SD1), R51.2, R52.2, R53.2, R54.2, R55.2, TP15.1 (1_1)
VDD_ETH_1V0: C34.1, C54.1, C57.1, C60.1, C63.1, C66.1, C69.1, C71.1, C73.1, C76.1, C79.1, U6.1 (OUT), U13.6 (VDD1P0), U13.24 (VDD1P0), U13.31 (VDD1P0), U13.42 (VDD1P0)
VDD_ETH_2V5: C33.1, C55.1, C58.1, C61.1, C64.1, C67.1, C70.1, Q2.1 (G), R17.1, R91.1, U5.1 (OUT), U13.3 (VDDA2P5), U13.9 (VDDA2P5)
X_BOOT_MODE0: J1.B33 (X_BOOT_MODE0), R43.1, SW3.1, TP11.1 (1_1)
X_BOOT_MODE1: J1.B34 (X_BOOT_MODE1), R44.1, SW3.2, TP12.1 (1_1)
X_BOOT_MODE2: J1.B35 (X_BOOT_MODE2), R45.1, SW3.3, TP13.1 (1_1)
X_BOOT_MODE3: J1.B36 (X_BOOT_MODE3), R46.1, SW3.4, TP14.1 (1_1)
X_CONN_ETH1_PHY_INT: R66.1, U13.44 (INT/PWDN)
X_ENET0_MDC: J1.A68 (X_ENET0_MDC), U13.16 (MDC)
X_ENET0_MDIO: J1.A67 (X_ENET0_MDIO), U13.17 (MDIO)
X_ESAI0_FSR/ENET1_RGMII_TXC: J1.B39 (X_ESAI0_FSR/ENET1_RGMII_TXC), U13.29 (GTX_CLK)
X_ESAI0_FST/ENET1_RGMII_TXD2: J1.B38 (X_ESAI0_FST/ENET1_RGMII_TXD2), U13.26 (TX_D2)
X_ESAI0_SCKR/ENET1_RGMII_TX_CTL: J1.B42 (X_ESAI0_SCKR/ENET1_RGMII_TX_CTL), U13.37 (TX_CTRL)
X_ESAI0_SCKT/ENET1_RGMII_TXD3: J1.B41 (X_ESAI0_SCKT/ENET1_RGMII_TXD3), U13.25 (TX_D3)
X_ESAI0_TX0/ENET1_RGMII_RXC: J1.B43 (X_ESAI0_TX0/ENET1_RGMII_RXC), R78.2
X_ESAI0_TX1/ENET1_RGMII_RXD3: J1.B44 (X_ESAI0_TX1/ENET1_RGMII_RXD3), R76.2
X_ESAI0_TX2_RX3/ENET1_RGMII_RXD2: J1.B46 (X_ESAI0_TX2_RX3/ENET1_RGMII_RXD2), R67.2, R68.1, R75.2
X_ESAI0_TX3_RX2/ENET1_RGMII_RXD1: J1.B47 (X_ESAI0_TX3_RX2/ENET1_RGMII_RXD1), R74.2
X_ESAI0_TX4_RX1/ENET1_RGMII_TXD0: J1.B48 (X_ESAI0_TX4_RX1/ENET1_RGMII_TXD0), U13.28 (TX_D0)
X_ESAI0_TX5_RX0/ENET1_RGMII_TXD1: J1.B49 (X_ESAI0_TX5_RX0/ENET1_RGMII_TXD1), U13.27 (TX_D1)
X_ETH0_A_TX_N: J1.B68 (X_ETH0_A-/TX0-/MAC_TXD2), T1.2 (D1-), TV2.1
X_ETH0_A_TX_P: J1.B69 (_X_ETH0_A+/TX0+/MAC_TXD3), T1.1 (D1+), TV2.3
X_ETH0_B_TX_N: J1.B66 (X_ETH0_B-/RX0-/MAC_TXD0), T1.6 (D2-), TV1.1
X_ETH0_B_TX_P: J1.B67 (X_ETH0_B+/RX0+/MAC_TXD1), T1.3 (D2+), TV2.4
X_ETH0_C_TXCLK_N: J1.B64 (X_ETH0_C-/MAC_TXEN), T1.5 (D3-), TV2.6
X_ETH0_C_TXCLK_P: J1.B65 (X_ETH0_C+/MAC_TXCLK), T1.4 (D3+), TV1.3
X_ETH0_D_RXDV_N: J1.B61 (X_ETH0_D-/MAC_CLK), T1.8 (D4-), TV1.4
X_ETH0_D_RXDV_P: J1.B62 (X_ETH0_D+/MAC_RXDV), T1.7 (D4+), TV1.6
X_ETH0_LED0: J1.A62 (X_ETH0_LED0/MAC_RXD3), R92.1, R94.2
X_ETH0_LED1: J1.A63 (X_ETH0_LED1/MAC_RXD2), R93.2, R95.2
X_ETH_GPIO0: J1.A64 (X_ETH_GPIO0), R81.2, R82.1, U13.39 (GPIO_0)
X_ETH_GPIO1: J1.A65 (X_ETH_GPIO1), U13.40 (GPIO_1)
X_FLEXCAN1_RX: J1.A43 (X_FLEXCAN1_RX), U33.4 (R)
X_FLEXCAN1_TX: J1.A44 (X_FLEXCAN1_TX), U33.1 (D)
X_JTAG_TCK: J1.D51 (X_JTAG_TCK), R146.1
X_JTAG_TDI: J1.D53 (X_JTAG_TDI), R147.1
X_JTAG_TDO: J1.D52 (X_JTAG_TDO), R148.1
X_JTAG_TMS: J1.D54 (X_JTAG_TMS), R149.1
X_PGOOD: CN3.9, J1.C53 (X_PGOOD), R127.2, TP1.1 (1_1), U3.3 (ON)
X_PMIC_WDI: J1.C60 (X_PMIC_WDI), JP1.2 (B)
X_QSPI0A_SCLK: J1.C3 (X_QSPI0A_SCLK), U9.16 (SCLK)
X_QSPI0A_SS1_B: J1.C2 (X_QSPI0A_SS1_B), U9.7 (CS#)
X_QSPI0_DATA0: J1.D1 (X_QSPI0_DATA0), U9.15 (SI/SIO0)
X_QSPI0_DATA1: J1.D2 (X_QSPI0_DATA1), U9.8 (SO/SIO1)
X_QSPI0_DATA2: J1.D3 (X_QSPI0_DATA2), U9.9 (SIO2)
X_QSPI0_DATA3: J1.D4 (X_QSPI0_DATA3), U9.1 (SIO3)
X_QSPI0_DATA4: J1.D6 (X_QSPI0_DATA4), U9.14 (SIO4)
X_QSPI0_DATA5: J1.D7 (X_QSPI0_DATA5), U9.5 (SIO5)
X_QSPI0_DATA6: J1.D8 (X_QSPI0_DATA6), U9.12 (SIO6)
X_QSPI0_DATA7: J1.D9 (X_QSPI0_DATA7), U9.4 (SIO7)
X_SPDIF0_EXT_CLK/ENET1_REFCLK_12: J1.B53 (X_SPDIF0_EXT_CLK/ENET1_REFCLK_12), R83.1
X_SPDIF0_RX/ENET1_RGMII_RXD0: J1.B51 (X_SPDIF0_RX/ENET1_RGMII_RXD0), R69.2, R70.1, R73.2
X_SPDIF0_TX/ENET1_RGMII_RX_CTL: J1.B52 (X_SPDIF0_TX/ENET1_RGMII_RX_CTL), R77.2, R84.2, R85.1
X_SPI0_CS0: J1.A26 (X_SPI0_CS0), U11.1 (~CS)
X_SPI0_CS1: J1.A28 (X_SPI0_CS1), U12.1 (~CS)
X_SPI0_SCK: J1.A27 (X_SPI0_SCK), U11.6 (SCK), U12.6 (SCK)
X_SPI0_SDI: J1.A30 (X_SPI0_SDI), U11.2 (SO), U12.2 (SO)
X_SPI0_SDO: J1.A29 (X_SPI0_SDO), U11.5 (SI), U12.5 (SI)
X_SPI2_CS0: J1.A21 (X_SPI2_CS0), U10.2 (DAT3/CS)
X_SPI2_SCK: J1.A22 (X_SPI2_SCK), U10.3 (CLK)
X_SPI2_SDI: J1.A23 (X_SPI2_SDI), U10.7 (DAT0/MISO)
X_SPI2_SDO: J1.A24 (X_SPI2_SDO), U10.8 (CMD/MOSI)
X_SPI3_CS0: CN4.14, J1.B55 (X_SPI3_CS0)
X_SPI3_SCK: CN4.16, J1.B57 (X_SPI3_SCK)
X_SPI3_SDI: CN4.15, J1.B58 (X_SPI3_SDI)
X_SPI3_SDO: CN4.13, J1.B59 (X_SPI3_SDO)
X_UART0_RX: J1.A49 (X_UART0_RX), U29.4 (1A)
X_UART0_TX: J1.A48 (X_UART0_TX), U29.7 (2A)
X_UART1_CTS_B: J1.A57 (X_UART1_CTS_B), JP2.1 (A)
X_UART1_RTS_B: J1.A58 (X_UART1_RTS_B), JP3.1 (A)
X_UART1_RX: J1.A59 (X_UART1_RX), U17.3 (1R)
X_UART1_TX: J1.A60 (X_UART1_TX), U17.15 (1D)
X_UART2_RX: J1.A50 (X_UART2_RX), U22.20 (TXD)
X_UART2_TX: J1.A51 (X_UART2_TX), U22.21 (RXD)
X_UART3_RX: J1.A47 (X_FLEXCAN2_RX), J8.13
X_UART3_TX: J1.A46 (X_FLEXCAN2_TX), J8.15
X_USB_OTG1_DN: J1.A4 (X_USB_OTG1_DN), R100.2
X_USB_OTG1_DP: J1.A3 (X_USB_OTG1_DP), R101.2
X_USB_OTG2_DN: J1.B4 (X_USB_OTG2_DN), R105.2
X_USB_OTG2_DP: J1.B5 (X_USB_OTG2_DP), R104.2
X_USDHC1_CD_B/NAND_DQS_P: Card1.9 (SW), J1.A10 (X_USDHC1_CD_B/NAND_DQS_P), R56.1
X_USDHC1_CLK: Card1.5 (CLK), J1.A18 (X_USDHC1_CLK), R53.1
X_USDHC1_CMD/NAND_CE0_B: J1.A19 (X_USDHC1_CMD/NAND_CE0_B), R59.2
X_USDHC1_DATA0/NAND_CE1_B: J1.A16 (X_USDHC1_DATA0/NAND_CE1_B), R54.1, R60.2
X_USDHC1_DATA1/NAND_RE_B: J1.A15 (X_USDHC1_DATA1/NAND_RE_B), R55.1, R61.2
X_USDHC1_DATA2/NAND_WE_B: J1.A14 (X_USDHC1_DATA2/NAND_WE_B), R51.1, R57.2
X_USDHC1_DATA3/NAND_ALE: J1.A13 (X_USDHC1_DATA3/NAND_ALE), R52.1, R58.2
X_USDHC1_RESET_B/NAND_RE_N: J1.A11 (X_USDHC1_RESET_B/NAND_RE_N), U8.A3 (EN)
X_nRESET_IN: D9.2 (A), J1.C46 (X_nRESET_IN), SW2.1, SW2.2, TP9.1 (1_1)
uSD_Power: R56.2, TP16.1 (1_1), U8.B1 (VOUT)

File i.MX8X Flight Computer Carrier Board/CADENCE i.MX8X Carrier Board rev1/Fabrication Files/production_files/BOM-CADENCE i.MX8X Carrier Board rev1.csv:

Comment,Designator,Footprint,LCSC,Quantity
0,R78,R_0402_1005Metric,C15402,1
0.002,"R122,R126,R155,R157,R159",R_1206_3216Metric,C843877,5
1.47k,R18,R_0603_1608Metric,C22841,1
1.8uH,L1,IND-SMD_L6.6-W6.4-P4.04_XAL6030-182MEC,C19191693,1
10,R25,R_1206_3216Metric,C17903,1
100,R128,R_0402_1005Metric,C25076,1
100k,"R153,R35,R37,R38,R40,R41,R8",R_0402_1005Metric,C25741,7
100nF,"C35,C5",C_0603_1608Metric,C1591,2
100nF,"C100,C101,C102,C104,C105,C106,C108,C109,C11,C111,C112,C113,C114,C117,C119,C120,C121,C123,C125,C126,C129,C131,C133,C135,C136,C139,C14,C15,C16,C18,C27,C28,C29,C30,C33,C34,C45,C47,C48,C49,C50,C51,C56,C57,C58,C62,C63,C64,C68,C69,C73,C78,C81,C84,C85,C87,C89,C92,C93,C95,C96,C97",C_0402_1005Metric,C77020,62
100uF,"C37,C38,C39",CAP-SMD_L7.3-W6.1_TCN4227M025R0100,C2158793,3
10K,"R127,R129,R132,R133,R138,R139,R141,R145,R160,R161,R67,R72,R80,R86,R90,R91,R95,R99",R_0402_1005Metric,C60490,18
10k,"R124,R125,R130,R16,R17,R26,R27,R28,R29,R32,R33,R43,R44,R45,R46,R62,R63,R64,R65,R94",R_0402_1005Metric,C60490,20
10nF,C10,C_0402_1005Metric,C1524,1
10nF,"C67,C74,C76,C82",C_0603_1608Metric,C1589,4
10nF,C7,C_0402_1005Metric,C60133,1
10pF,C22,C_0402_1005Metric,C1545,1
10u,C94,C_0805_2012Metric,C15850,1
10u,C98,C_0603_1608Metric,C19702,1
10u,"C40,C41,C42,C43,C44",C0402,C315248,5
10uF,"C127,C130,C46,C70,C75,C79,C83",C_0603_1608Metric,C18800,7
120,"R106,R107,R15,R154",R_0402_1005Metric,C22787,4
12K,R142,R_0402_1005Metric,C25535,1
12MHz,Y2,CRYSTAL-SMD_4P-L3.2-W2.5-BL,C9002,1
12pF,"C115,C116",C_0603_1608Metric,C1642,2
150,"R156,R158",R_0402_1005Metric,C82683,2
15k,"R19,R24",R_0402_1005Metric,C25756,2
16.5K,R131,R_0402_1005Metric,C226807,1
16P8WGJ103T4E,"RN2,RN3,RN4",RES-ARRAY-SMD_0402-16P-L4.0-W1.6-BL,C61520,3
18.2k,"R6,R7",R_0402_1005Metric,C25859,2
18pF,"C52,C53",C_0402_1005Metric,C1549,2
1K,"R144,R152,R79",R_0402_1005Metric,C11702,3
1M,"R71,R9",R_0603_1608Metric_Pad0.98x0.95mm_HandSolder,C22935,2
1M,"R10,R22",R_0402_1005Metric,C26083,2
1N4448WS-7-F,"D6,D8",SOD-323_L1.8-W1.3-LS2.5-RD,C2979762,2
1k,"R34,R36,R47,R48,R49,R50",R0402,C11702,6
1nF,"C32,C86,C88,C90,C91",C_0402_1005Metric,C1523,5
1uF,"C107,C12,C128,C132,C54,C55,C59,C60,C61,C65,C66,C71,C72,C77,C80,C9",C_0603_1608Metric,C29936,16
2.2uF,C103,C_0603_1608Metric,C1607,1
2.49K,"R68,R69,R70,R82,R85,R87,R89,R98",R_0402_1005Metric,C102924,8
2.5uH,L2,IND-SMD_L10.9-W10.0,C409642,1
200,"R143,R92,R93,R97",R_0402_1005Metric,C25087,4
22,"R1,R123,R136,R137,R146,R147,R148,R149,R150,R151,R2,R3,R4,R5,R57,R58,R59,R60,R61,R73,R74,R75,R76,R77,R96",R_0402_1005Metric,C25092,25
220nF,C99,C_0603_1608Metric,C1606,1
22uF,"C137,C138,C17,C19",C_0805_2012Metric,C29277,4
22uF,C1,C_0603_1608Metric,C59461,1
22uF,C2,C_0603_1608Metric,C69335,1
23.7k,R14,R_0402_1005Metric,C22912,1
243k,R12,R_0402_1005Metric,C278587,1
25MHz,Y1,CRYSTAL-SMD_4P-L3.2-W2.5-BL-2,C13740,1
27,"R100,R101,R104,R105",R_0402_1005Metric,C25156,4
2K,"R140,R66",R_0402_1005Metric,C4109,2
330,R21,R_0603_1608Metric,C22104,1
330,"R108,R109,R114,R115,R116,R117",R_0402_1005Metric,C25104,6
33pF,C36,C_0402_1005Metric,C1562,1
360,R13,R_0603_1608Metric,C25194,1
3k,"R30,R31",R0402,C2909355,2
4.7M,R39,R0402,C474132,1
4.7k,"R110,R111,R112,R113,R118,R119,R120,R121",R_0402_1005Metric,C25900,8
4.7pF,C21,C_0402_1005Metric,C1569,1
4.7uF,"C110,C118,C122,C124,C13,C134,C26,C3,C31,C4,C6,C8",C_0603_1608Metric,C69335,12
4.7uH,L3,IND-SMD_L7.0-W6.6,C167220,1
412k,R11,R_0402_1005Metric,C2092057,1
43,R42,R_0402_1005Metric,C131584,1
470,R20,R_0603_1608Metric,C23179,1
47uF,"C20,C23,C24,C25",C_0805_2012Metric,C76636,4
49.9,R83,R_0402_1005Metric,C25120,1
49.9k,"R51,R52,R53,R54,R55,R56",R_0402_1005Metric,C137969,6
4D02WGJ0103TCE,RN1,RES-ARRAY-SMD_0402-8P-L2.0-W1.0-BL,C25725,1
5.1k,"R102,R103,R134,R135",R_0402_1005Metric,C25905,4
5.76K,"R81,R84,R88",R_0402_1005Metric,C881162,3
5027740891,Card1,HRS_DM3BT-DSF-PEJS,C597972,1
600R/100MHz,"L4,L5",L0805,C1017,2
74CBTLV3257BQ,U29,74CBTLV3257BQ115,C546449,1
74LVC2G07,U14,SOT-363_L2.1-W1.3-P0.65-LS2.2-BL,C24478,1
90.9k,R23,R_0402_1005Metric,C26989,1
BD2204GUL-E2,U8,BGA-6_L1.5-W1.0-P0.50_BD2204GUL-E2,C314699,1
BLUE,D3,LED_0603_1608Metric,C2288,1
BSS138,"Q2,Q3",SOT-23,C8490,2
BTH-070-02-L-D-A,J1,SAMTEC_BTH-070-02-L-D-A,C20355608,1
Battery_Cell,"BT1,BT2",BAT-SMD_MY-2032-11,C964835,2
CAT93C66VI-GT3,U30,SOIC-8_L4.9-W3.9-P1.27-LS6.0-BL,C890471,1
Conn_01x08,J7,CONN_BM08B-SRSS-TBLFSN_JST,C160394,1
Conn_Coaxial,J4,SMA-TH_132134,C3174425,1
DF11-16DP-2DSA(08),"CN1,CN2,CN3,CN4",CONN-TH_DF11-16DP-2DSA-08,C530981,4
DP83867IRRGZR,U13,VQFN-48_L7.0-W7.0-P0.50-BL-EP4.1,C544766,1
FT2232HL,U32,LQFP-64_L10.0-W10.0-P0.50-LS12.0-TL,C27882,1
GREEN,"D2,D4,D7",LED_0603_1608Metric,C2289,3
INA219AxDCN,"U21,U27,U34,U36,U38",SOT-23-8,C87469,5
IRLML6401,Q1,SOT-23,C3034,1
KMR221GLFS,SW2,KEY-SMD_KMR2XXGXXX,C72443,1
LP38693MP-ADJ/NOPB,U28,SOT-223-5_L6.5-W3.5-P1.50-LS7.0-BL,C181420,1
LSM6DSO,U24,LGA-14_L3.0-W2.5-P0.50-TL,C2655100,1
LT8612,"U1,U2",QFN-28_UDE_LTI,C580313,2
MBR0520LT,"D10,D11",D_SOD-123,C23848,2
P82B715DR,"U18,U19,U20",SOIC127P600X175-8N,C2649394,3
RED,"D1,D5,D9",LED_0603_1608Metric,C2286,3
RV-3028-C7,U23,MicroCrystal_C7_SON-8_1.5x3.2mm_P0.9mm,C3019759,1
SN65C1168ERGYR,U17,SOP-16_4.55x10.3mm_P1.27mm,C529555,1
SN65HVD233,U33,SOIC-8_3.9x4.9mm_P1.27mm,C61643,1
SRV05-4.TCT,"TV1,TV2,TV3,TV4,TV5",SOT-23-6_L2.9-W1.6-P0.95-LS2.8-BR,C13612,5
SW_DIP_x01,"SW1,SW4",SW-SMD_1.27-1P-TPPT,C6386918,2
SW_DIP_x04,SW3,SW-SMD_8P-L11.3-W6.2-P1.27-LS8.2,C266192,1
TLV1704,U7,TSSOP-14_4.4x5mm_P0.65mm,C181596,1
TLV71310PDQNR,U6,X2SON-4_L1.0-W1.0-P0.65-TL-EP,C2872754,1
TLV71325PDQNR,U5,X2SON-4_L1.0-W1.0-P0.65-TL-EP,C2872754,1
TMP112xxDRL,U26,SOT-563,C28927,1
TPS22810DBV,U37,SOT-23-6,C205990,1
TPS22810DBV,U35,SOT-23-6,C2680364,1
TPS22975,U39,DSG0008B,C2149871,1
TPS22975,U3,DSG0008B,C524777,1
TXS0101DCKR,"U40,U41",SC-70-6_L2.0-W1.3-P0.65-LS2.1-BR,C132031,2
USBLC6-2SC6,"U15,U16,U31",SOT-23-6,C7519,3
USB_A,J3,SAMTEC_USB-A-S-X-X-TH,C3197723,1
USB_C_Receptacle_USB2.0_16P,"J2,J5",USB-C_SMD-TYPE-C-31-M-12,C165948,2
WE-RJ45_7499111121A,"T1,T2",7499111121A,C5523983,2
MX25UM51245G,U9,SOP-16_L10.3-W7.5-P1.27-LS10.3-BL,,1
Conn_01x01,J6,PinHeader_1x01_P1.00mm_Vertical,,1
